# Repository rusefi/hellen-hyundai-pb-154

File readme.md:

https://en.wikipedia.org/wiki/Hyundai-Kia_small_automobile_platforms

https://rusefi.com/docs/pinouts/hellen/hellen-hyundai-pb-mt/

same pinout for

2012-2017 Hyundai Accent

2012-2017 Kia Rio

2012-2017 Kia Soul 1.6

2013-2017 Hyundai Veloster 1.6 Turbo

2014-2017 Kia Forte 1.6 Turbo

https://github.com/rusefi/rusefi_documentation/tree/master/OEM-Docs/Kia

https://github.com/rusefi/rusefi_documentation/blob/master/OEM-Docs/Kia/2014-soul.pdf

https://github.com/rusefi/rusefi_documentation/blob/master/OEM-Docs/Kia/2015-koup.pdf?

https://github.com/rusefi/rusefi_documentation/tree/master/OEM-Docs/Hyundai

https://github.com/rusefi/rusefi_documentation/blob/master/OEM-Docs/Hyundai/2014-veloster.pdf ?

Not to be confused with MEFI https://github.com/rusefi/hellen154hyundai

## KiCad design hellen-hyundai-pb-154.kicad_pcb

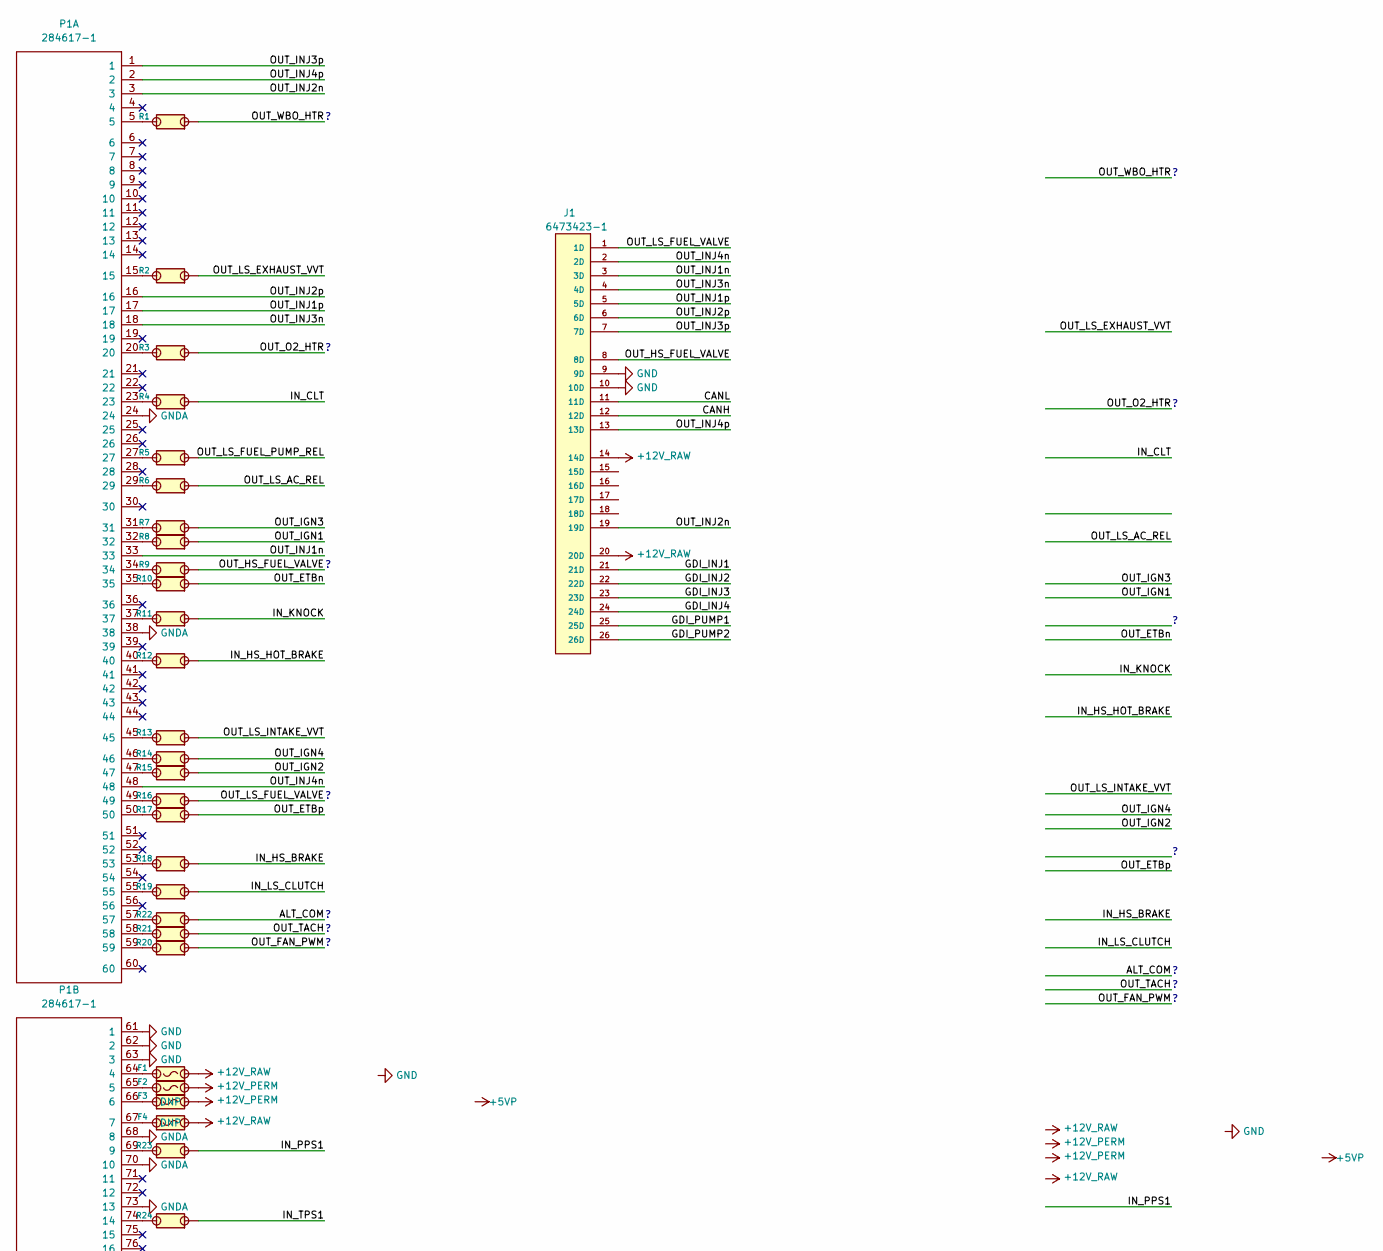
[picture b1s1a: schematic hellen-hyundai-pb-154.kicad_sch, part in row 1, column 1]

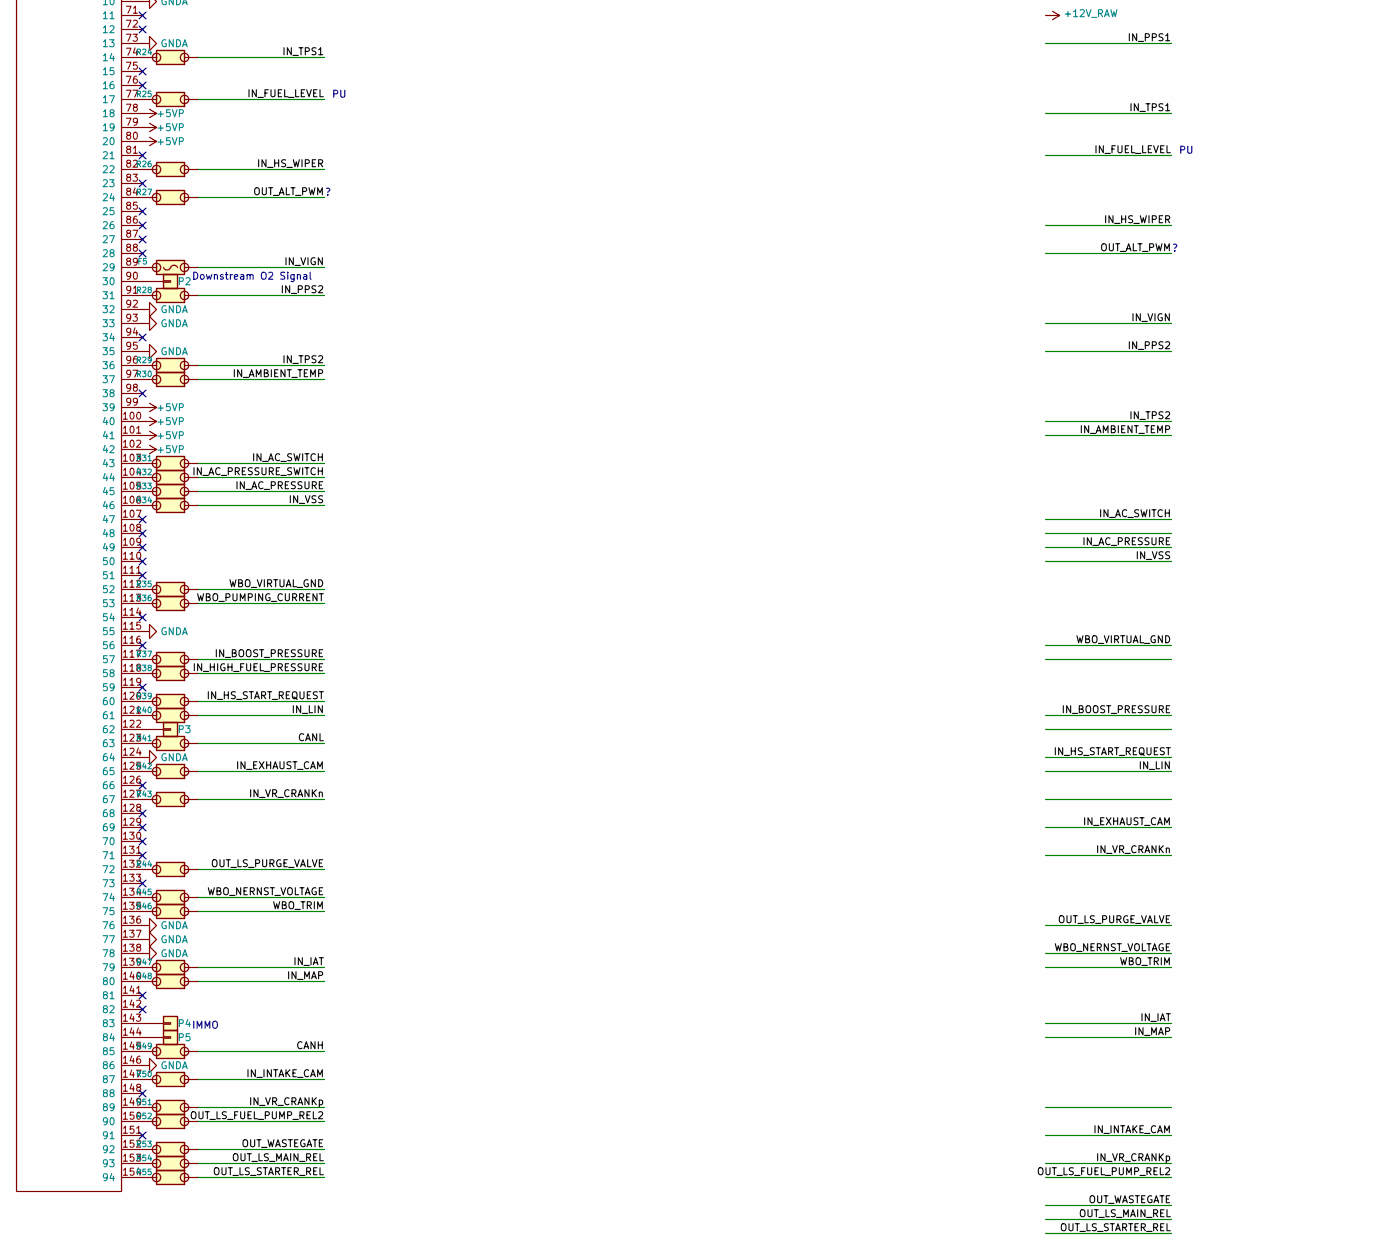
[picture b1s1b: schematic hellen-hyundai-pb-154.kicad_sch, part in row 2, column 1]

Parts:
F1, F2, F5: Fuse-Pad-Pad; PAD-1206-PAD; LCSC C182446
F3, F4: Fuse-Pad-Pad; PAD-1206-PAD
J1: 6473423-1
P1: 284617-1; TE_284617-1
P2, P3, P4, P5: Pad; PAD-TH
R1, R2, R3, R4, R5, R6, R7, R8, R9, R10, R11, R12, R13, R14, R15, R16, R17, R18, R19, R20, R21, R22, R23, R24, R25, R26, R27, R28, R29, R30, R31, R32, R33, R34, R35, R36, R37, R38, R39, R40, R41, R42, R43, R44, R45, R46, R47, R48, R49, R50, R51, R52, R53, R54, R55: Jumper-Pad-Pad; PAD-0805-PAD; LCSC C17477

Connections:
+5VP: P1.78 (18), P1.79 (19), P1.80 (20), P1.99 (39), P1.100 (40), P1.101 (41), P1.102 (42)
+12V_PERM: F2.2, F3.2
+12V_RAW: F1.2, F4.2, J1.14 (14D), J1.20 (20D)
/ALT_COM: R22.1
/CANH: J1.12 (12D), R49.1
/CANL: J1.11 (11D), R41.1
/GDI_INJ1: J1.21 (21D)
/GDI_INJ2: J1.22 (22D)
/GDI_INJ3: J1.23 (23D)
/GDI_INJ4: J1.24 (24D)
/GDI_PUMP1: J1.25 (25D)
/GDI_PUMP2: J1.26 (26D)
/IN_AC_PRESSURE: R33.1
/IN_AC_PRESSURE_SWITCH: R32.1
/IN_AC_SWITCH: R31.1
/IN_AMBIENT_TEMP: R30.1
/IN_BOOST_PRESSURE: R37.1
/IN_CLT: R4.1
/IN_EXHAUST_CAM: R42.1
/IN_FUEL_LEVEL: R25.1
/IN_HIGH_FUEL_PRESSURE: R38.1
/IN_HS_BRAKE: R18.1
/IN_HS_HOT_BRAKE: R12.1
/IN_HS_START_REQUEST: R39.1
/IN_HS_WIPER: R26.1
/IN_IAT: R47.1
/IN_INTAKE_CAM: R50.1
/IN_KNOCK: R11.1
/IN_LIN: R40.1
/IN_LS_CLUTCH: R19.1
/IN_MAP: R48.1
/IN_PPS1: R23.1
/IN_PPS2: R28.1
/IN_TPS1: R24.1
/IN_TPS2: R29.1
/IN_VIGN: F5.2
/IN_VR_CRANKn: R43.1
/IN_VR_CRANKp: R51.1
/IN_VSS: R34.1
/OUT_ALT_PWM: R27.1
/OUT_ETBn: R10.1
/OUT_ETBp: R17.1
/OUT_FAN_PWM: R20.1
/OUT_HS_FUEL_VALVE: J1.8 (8D), R9.1
/OUT_IGN1: R8.1
/OUT_IGN2: R15.1
/OUT_IGN3: R7.1
/OUT_IGN4: R14.1
/OUT_INJ1n: J1.3 (3D), P1.33
/OUT_INJ1p: J1.5 (5D), P1.17
/OUT_INJ2n: J1.19 (19D), P1.3
/OUT_INJ2p: J1.6 (6D), P1.16
/OUT_INJ3n: J1.4 (4D), P1.18
/OUT_INJ3p: J1.7 (7D), P1.1
/OUT_INJ4n: J1.2 (2D), P1.48
/OUT_INJ4p: J1.13 (13D), P1.2
/OUT_LS_AC_REL: R6.1
/OUT_LS_EXHAUST_VVT: R2.1
/OUT_LS_FUEL_PUMP_REL: R5.1
/OUT_LS_FUEL_PUMP_REL2: R52.1
/OUT_LS_FUEL_VALVE: J1.1 (1D), R16.1
/OUT_LS_INTAKE_VVT: R13.1
/OUT_LS_MAIN_REL: R54.1
/OUT_LS_PURGE_VALVE: R44.1
/OUT_LS_STARTER_REL: R55.1
/OUT_O2_HTR: R3.1
/OUT_TACH: R21.1
/OUT_WASTEGATE: R53.1
/OUT_WBO_HTR: R1.1
/WBO_NERNST_VOLTAGE: R45.1
/WBO_PUMPING_CURRENT: R36.1
/WBO_TRIM: R46.1
/WBO_VIRTUAL_GND: R35.1
GND: J1.9 (9D), J1.10 (10D), P1.61 (1), P1.62 (2), P1.63 (3)
GNDA: P1.24, P1.38, P1.68 (8), P1.70 (10), P1.73 (13), P1.92 (32), P1.93 (33), P1.95 (35), P1.115 (55), P1.124 (64), P1.136 (76), P1.137 (77), P1.138 (78), P1.146 (86)
unnamed: P1.5, R1.2
unnamed: P1.15, R2.2
unnamed: P1.20, R3.2
unnamed: P1.23, R4.2
unnamed: P1.27, R5.2
unnamed: P1.29, R6.2
unnamed: P1.31, R7.2
unnamed: P1.32, R8.2
unnamed: P1.34, R9.2
unnamed: P1.35, R10.2
unnamed: P1.37, R11.2
unnamed: P1.40, R12.2
unnamed: P1.45, R13.2
unnamed: P1.46, R14.2
unnamed: P1.47, R15.2
unnamed: P1.49, R16.2
unnamed: P1.50, R17.2
unnamed: P1.53, R18.2
unnamed: P1.55, R19.2
unnamed: P1.57, R22.2
unnamed: P1.58, R21.2
unnamed: P1.59, R20.2
unnamed: F1.1, P1.64 (4)
unnamed: F2.1, P1.65 (5)
unnamed: F3.1, P1.66 (6)
unnamed: F4.1, P1.67 (7)
unnamed: P1.69 (9), R23.2
unnamed: P1.74 (14), R24.2
unnamed: P1.77 (17), R25.2
unnamed: P1.82 (22), R26.2
unnamed: P1.84 (24), R27.2
unnamed: F5.1, P1.89 (29)
unnamed: P1.90 (30), P2.1
unnamed: P1.91 (31), R28.2
unnamed: P1.96 (36), R29.2
unnamed: P1.97 (37), R30.2
unnamed: P1.103 (43), R31.2
unnamed: P1.104 (44), R32.2
unnamed: P1.105 (45), R33.2
unnamed: P1.106 (46), R34.2
unnamed: P1.112 (52), R35.2
unnamed: P1.113 (53), R36.2
unnamed: P1.117 (57), R37.2
unnamed: P1.118 (58), R38.2
unnamed: P1.120 (60), R39.2
unnamed: P1.121 (61), R40.2
unnamed: P1.122 (62), P3.1
unnamed: P1.123 (63), R41.2
unnamed: P1.125 (65), R42.2
unnamed: P1.127 (67), R43.2
unnamed: P1.132 (72), R44.2
unnamed: P1.134 (74), R45.2
unnamed: P1.135 (75), R46.2
unnamed: P1.139 (79), R47.2
unnamed: P1.140 (80), R48.2
unnamed: P1.143 (83), P4.1
unnamed: P1.144 (84), P5.1
unnamed: P1.145 (85), R49.2
unnamed: P1.147 (87), R50.2
unnamed: P1.149 (89), R51.2
unnamed: P1.150 (90), R52.2
unnamed: P1.152 (92), R53.2
unnamed: P1.153 (93), R54.2
unnamed: P1.154 (94), R55.2

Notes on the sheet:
Downstream O2 Signal
IMMO

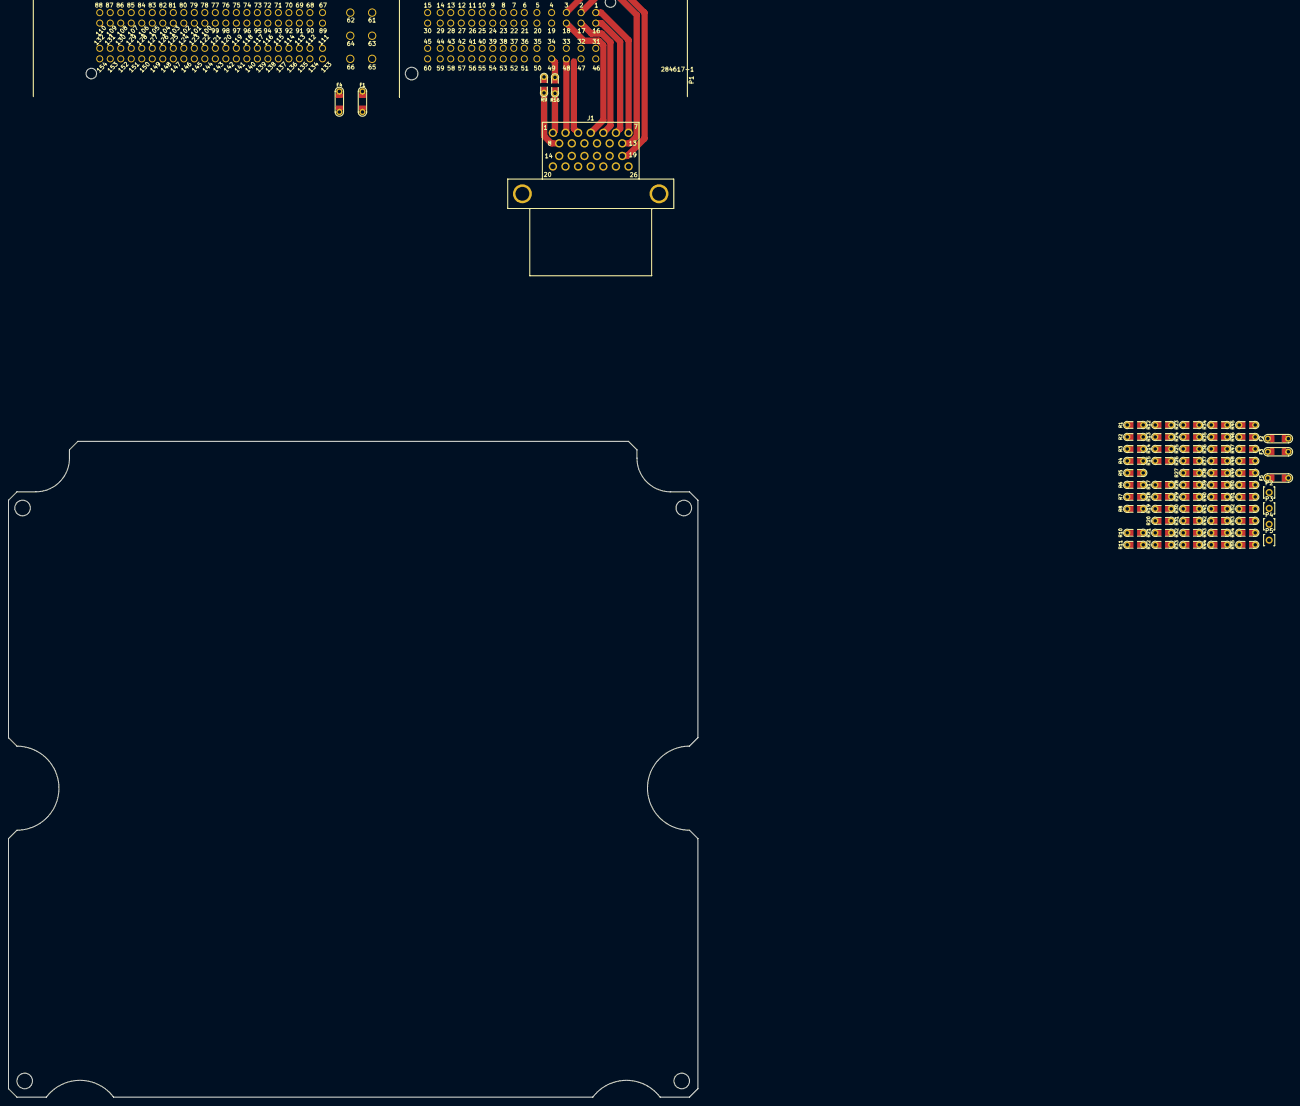
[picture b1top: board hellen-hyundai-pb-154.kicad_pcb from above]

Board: 4 copper layers, 164.0 x 156.0 mm, 66 parts (0 on the bottom side), 81 nets.

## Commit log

2023-04-18 hellen
2023-04-18 fancy
2023-04-20 Init project
2023-04-23 Pinout
2023-04-25 GDI pinout
2023-05-04 Upd SCH
2023-06-15 docs
2023-06-15 typo - it's dumb
2023-08-25 Revert "#26"
    This reverts commit 2a91b764912ec8b8fe29d716a56bad733d2ea11a.
